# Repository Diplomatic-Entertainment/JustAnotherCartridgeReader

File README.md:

# JustAnotherCartridgeReader (JACR)
### An Open Source Cartridge Reader Derivative

JACR uses modified Firmware based on the OSCR Firmware - 
[Original OSCR Project](https://github.com/sanni/cartreader)

## What makes the JACR different from OSCR?
- JACR is designed with a dedicated power circuity allowing both 5V and 3.3V at the same time.  
- JACR uses a different design for adapaters, the pins back to the microcontroller remain the same but the pin pitch is altered and more power pins were added.  
- [JACR Adapters](https://github.com/Diplomatic-Entertainment/JACR-Adapters) are currently designed with logic level converters.   
- **JACR is not directly compatible with OSCR adapers and JACR Adapters are not directly compatible with the OSCR**

## What is the same as the OSCR?
- JACR uses the MEGA2560 microconroller  
- JACR has the RTC and ClockGEN built into the main board  
- Support for all the same Systems as the OSCR  
- JACR complies with Open Source Licensing with source code available for viewing and modifying  

### Open Source Licenses:
Software(everything in Firmware folder) = GPL v3  
Hardware(everything in hardware folder) = CC BY 4.0  
Complies with the original license of the OSCR where applicable

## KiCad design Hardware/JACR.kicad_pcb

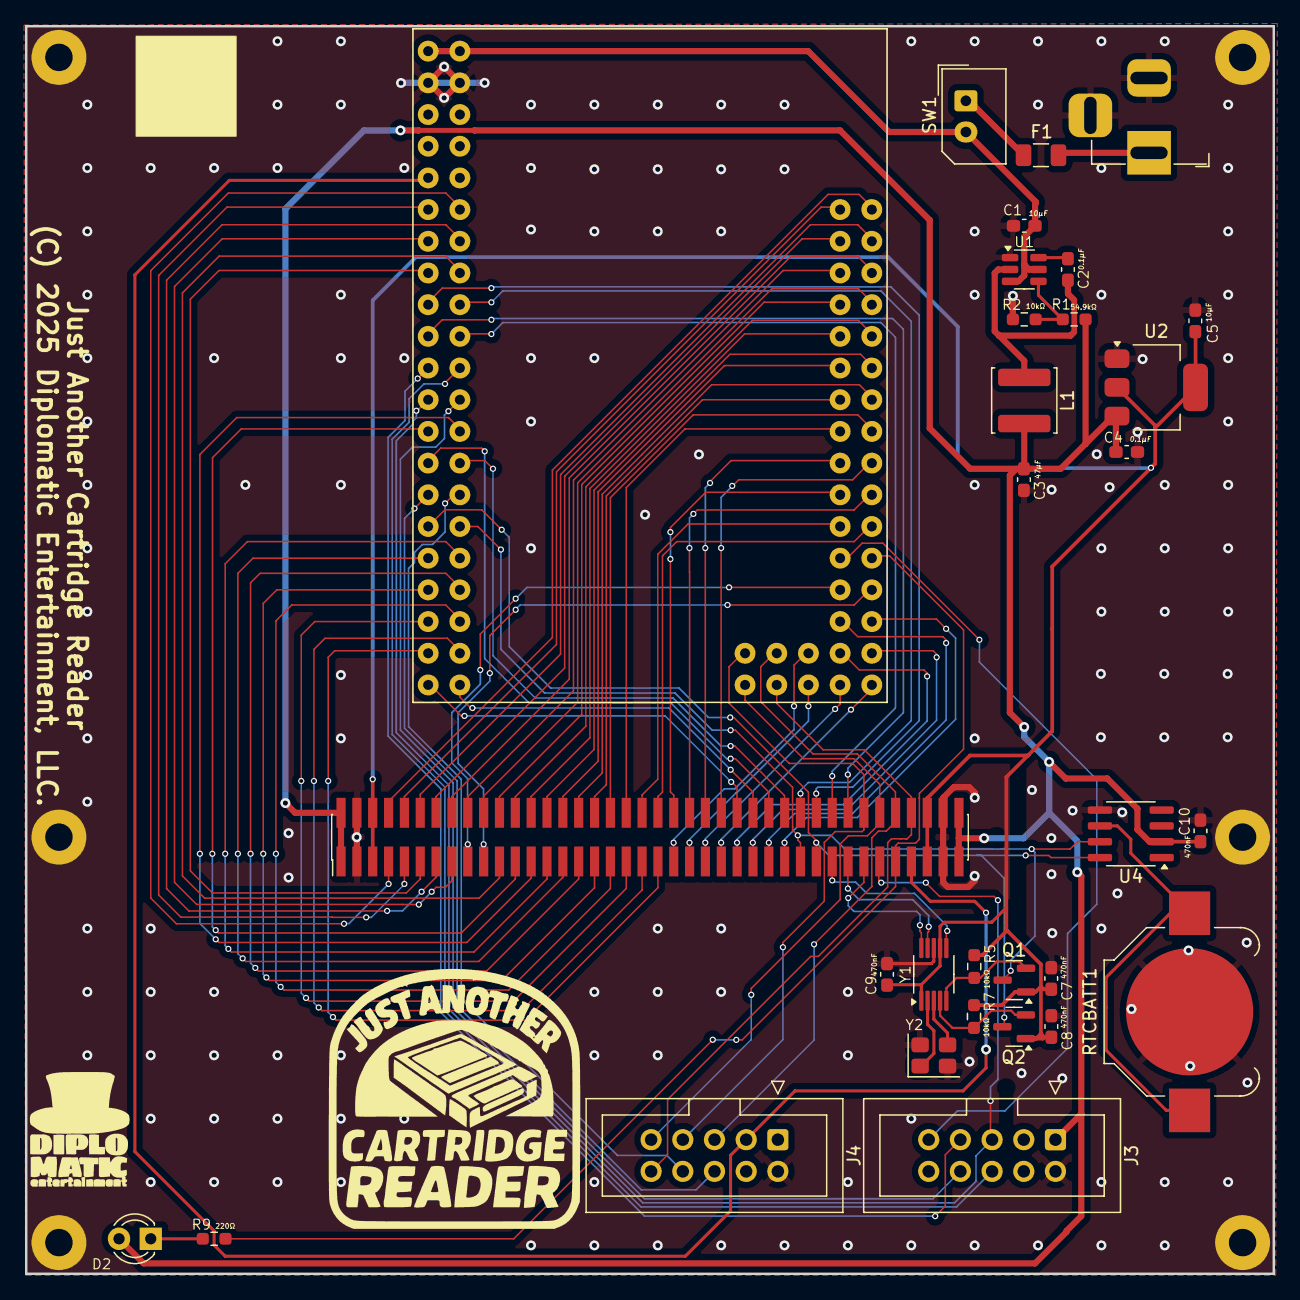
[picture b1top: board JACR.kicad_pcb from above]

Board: 2 copper layers, 100.0 x 100.0 mm, 38 parts (0 on the bottom side), 89 nets.

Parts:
BAR**: 2D Barcode 8mm
C1, C5: 10µF; C_0603_1608Metric_Pad1.08x0.95mm_HandSolder
C2, C4: 0.1µF; C_0603_1608Metric_Pad1.08x0.95mm_HandSolder
C3: 47µF; C_0603_1608Metric_Pad1.08x0.95mm_HandSolder
C7, C8, C9, C10: 470nF; C_0603_1608Metric_Pad1.08x0.95mm_HandSolder
D2: LED; LED_D3.0mm_Clear
F1: 1A; Fuse_1206_3216Metric
J1: Barrel_Jack_Switch; BarrelJack_Horizontal
J2: JACR CARTRIDGE SLOT; PinHeader_2x40_P1.27mm_Vertical_SMD
J3: EXP1; IDC-Header_2x05_P2.54mm_Vertical
J4: EXP2; IDC-Header_2x05_P2.54mm_Vertical
L1: 4.7µH; L_APV_ANR5040
M1, M2, M3, M4, M4#2, M4#3: MountingHole_2.2mm_M2_Pad
Q1, Q2: BSS138; SOT-23
R1: 54.9kΩ; R_0603_1608Metric_Pad0.98x0.95mm_HandSolder
R2, R5, R7: 10kΩ; R_0603_1608Metric_Pad0.98x0.95mm_HandSolder
R9: 220Ω; R_0603_1608Metric_Pad0.98x0.95mm_HandSolder
RTCBATT1: Battery_Cell; BatteryHolder_Keystone_3000_1x12mm
SW1: SW_SPST; Molex_SPOX_5267-02A_1x02_P2.50mm_Vertical
U1: TPS562200; SOT-23-6
U2: LD1117S33; SOT-223-3_TabPin2
U4: DS3231MZ; SOIC-8_3.9x4.9mm_P1.27mm
U5: MEGA PRO EMBEDED 2560; MODULE_MEGA_PRO_EMBED_CH340G___ATMEGA2560_SMD
Y1: Si5351A-B-GT; MSOP-10_3x3mm_P0.5mm
Y2: 25Mhz; Crystal_SMD_3225-4Pin_3.2x2.5mm

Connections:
+3V3: C5.1, C7.1, C8.1, C9.1, J2.5 (+3V3), J2.6 (+3V3), J2.75 (+3V3), J2.76 (+3V3), Q1.1 (G), Q2.1 (G), R5.1, R7.1, U2.2 (VO), Y1.1 (VDD), Y1.7 (VDDO)
+5V: C3.1, C4.1, C10.1, D2.2 (A), J2.1 (+5V), J2.2 (+5V), J2.79 (+5V), J2.80 (+5V), J3.1, L1.2, R1.1, U2.3 (VI), U4.2 (VCC)
/SCL: Q2.2 (S), R7.2, Y1.4 (SCL)
/SDA: Q1.2 (S), R5.2, Y1.5 (SDA)
/VBAT: RTCBATT1.1 (+), U4.6 (VBAT)
A0: J2.8 (A0), U5.A0
A1: J2.10 (A1), U5.A1
A2: J2.12 (A2), U5.A2
A3: J2.14 (A3), U5.A3
A4: J2.16 (A4), U5.A4
A5: J2.18 (A5), U5.A5
A6: J2.20 (A6), U5.A6
A7: J2.22 (A7), U5.A7
A8: J2.24 (A8), U5.A8
A9: J2.26 (A9), U5.A9
A10: J2.28 (A10), U5.A10
A11: J2.30 (A11), U5.A11
A12: J2.32 (A12), U5.A12
A13: J2.34 (A13), U5.A13
A14: J2.36 (A14), U5.A14
A15: J2.38 (A15), U5.A15
CLK0: J2.67 (CLK0), Y1.10 (CLK0)
CLK1: J2.65 (CLK1), Y1.9 (CLK1)
CLK2: J2.63 (CLK2), Y1.6 (CLK2)
D0: J2.7 (D0), U5.RX_D0
D1: J2.9 (D1), U5.TX_D1
D2: J2.13 (D2), U5.D2
D3: J2.15 (D3), U5.D3
D4: J2.21 (D4), U5.D4
D5: J2.11 (D5), U5.D5
D6: J2.60 (D6), U5.D6
D7: J2.62 (D7), U5.D7
D8: J2.64 (D8), U5.D8
D9: J2.66 (D9), U5.D9
D10: J3.6, U5.D10
D11: J3.7, U5.D11
D12: J3.8, U5.D12
D13: J2.69 (D13), J3.5, U5.D13
D14: J2.25 (D14), U5.D14
D15: J2.23 (D15), U5.D15
D16: J2.58 (D16), U5.D16
D17: J2.56 (D17), U5.D17
D18: J4.8, U5.D18
D19: J4.6, U5.D19
D20: J2.59 (D20), Q1.3 (D), U4.7 (SDA), U5.D20
D21: J2.61 (D21), Q2.3 (D), U4.8 (SCL), U5.D21
D22: J2.27 (D22), U5.D22
D23: J2.29 (D23), U5.D23
D24: J2.31 (D24), U5.D24
D25: J2.33 (D25), U5.D25
D26: J2.35 (D26), U5.D26
D27: J2.37 (D27), U5.D27
D28: J2.39 (D28), U5.D28
D29: J2.41 (D29), U5.D29
D30: J2.54 (D30), U5.D30
D31: J2.52 (D31), U5.D31
D32: J2.50 (D32), U5.D32
D33: J2.48 (D33), U5.D33
D34: J2.46 (D34), U5.D34
D35: J2.44 (D35), U5.D35
D36: J2.42 (D36), U5.D36
D37: J2.40 (D37), U5.D37
D38: J2.71 (D38), R9.2, U5.D38
D39: J3.9, U5.D39
D40: J2.19 (D40), U5.D40
D41: J2.17 (D41), U5.D41
D42: J2.57 (D42), U5.D42
D43: J2.55 (D43), U5.D43
D44: J2.53 (D44), U5.D44
D45: J2.51 (D45), U5.D45
D46: J2.49 (D46), U5.D46
D47: J2.47 (D47), U5.D47
D48: J2.45 (D48), U5.D48
D49: J2.43 (D49), U5.D49
D50: J2.74 (D50), J4.10, U5.D50
D51: J2.72 (D51), J4.5, U5.D51
D52: J2.70 (D52), J4.9, U5.D52
D53: J2.68 (D53), J4.7, U5.D53
GND: C1.2, C3.2, C4.2, C5.2, C7.2, C8.2, C9.2, C10.2, J1.2, J1.3, J2.3 (GND), J2.4 (GND), J2.77 (GND), J2.78 (GND), J3.2, J4.2, M1.1, M2.1, M3.1, M4.1, M4#2.1, M4#3.1, R2.2, RTCBATT1.2 (-), U1.1 (GND), U2.1 (GND), U4.5 (GND), U5.GND_1, U5.GND_2, Y1.8 (GND), Y2.2, Y2.4
unnamed: D2.1 (K), R9.1
unnamed: F1.1, J1.1
unnamed: F1.2, SW1.1 (A)
unnamed: C2.1, L1.1, U1.2 (SW)
unnamed: C2.2, U1.6 (VBST)
unnamed: R1.2, R2.1, U1.4 (VFB)
unnamed: Y1.2 (XA), Y2.1
unnamed: Y1.3 (XB), Y2.3
RST: J2.73 (RESET), J4.3, U5.RST
VCC: C1.1, SW1.2 (B), U1.3 (VIN), U1.5 (EN), U5.VIN_1, U5.VIN_2

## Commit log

2025-10-23 commiting all current modification
2025-10-23 Corrected reference to cart_reader folder to firmware folder
2025-10-23 Fix readme formatting
2025-11-02 Wrong Resistor values for the power regulator circuit
    Not sure where I got the old values but rereading the data sheet and testing is key to not overvolt anything
2025-11-06 Reroute traces going to the display connectors
    Added logos as well
2025-11-07 Modified power circuitry
    Changed inductor to a more readily available part
    Simplified 3.3V rail to linear regulator part
    After some testing, reduced fuse value, the whole unit barely hits 1 amp, might be higher during dumping
2025-11-07 Fixing references
    Undoing some prior changes while working thru debugging and updated references to OSCR to JACR
2025-11-07 Self Test changes
    Removed 1K Resistor test (Only Applicable to the N64 Controller)
    Removed rest on failure in Self Test
2025-11-08 Widen 3.3V rail traces
2025-11-10 Modified Clock Gnerator/RTC Circuit
    I believe putting the RTC I2C lines behind the transistors and pullups is causing problems with it not registering as present all the time. It may also be interfering with the Clock Generator.
2025-11-10 Changing the Mega2560 footprint back to through-hole
    Making it SMD seems to have provided no benefits and may have actually caused issues regarding data transfer.
    Currently no successful dump of any cartridge has occurred.
2025-11-10 Updated board images
2025-11-25 Corrected Source and Drain inputs on BSS138 in clock generator circuit
    It would seem I have the 3V and 5V flipped and may have been the cause of my clock generator appearing to not work
    also made adjustments to some traces

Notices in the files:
Hardware/JACR.kicad_pcb:
(C) 2025 Diplomatic Entertainment, LLC.
